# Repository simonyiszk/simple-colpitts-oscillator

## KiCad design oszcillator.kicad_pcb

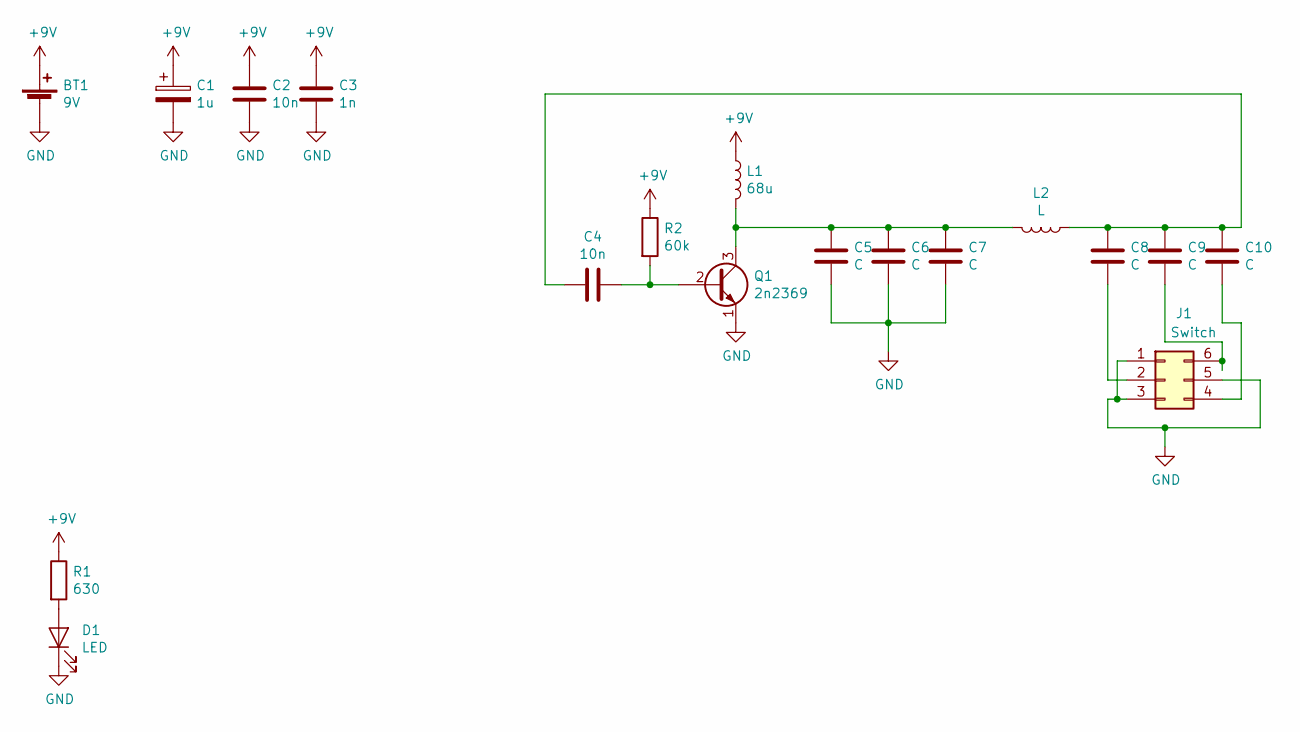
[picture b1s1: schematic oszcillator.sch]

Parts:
BT1: 9V; PinHeader_1x02_P2.54mm_Vertical
C1: 1u; CP_Radial_D6.3mm_P2.50mm
C2, C4: 10n; C_Disc_D3.4mm_W2.1mm_P2.50mm
C3: 1n; C_Disc_D3.4mm_W2.1mm_P2.50mm
C5, C6, C7, C8, C9, C10: C; C_Disc_D3.4mm_W2.1mm_P2.50mm
D1: LED; LED_D3.0mm
J1: Switch; PinSocket_2x03_P2.54mm_Vertical
L1: 68u; L_Axial_L5.3mm_D2.2mm_P10.16mm_Horizontal_Vishay_IM-1
L2: L; PinHeader_1x02_P2.54mm_Vertical
Q1: 2n2369; TO-18-3
R1: 630; R_Axial_DIN0204_L3.6mm_D1.6mm_P2.54mm_Vertical
R2: 60k; R_Box_L8.4mm_W2.5mm_P5.08mm

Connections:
+9V: BT1.1 (+), C1.1, C2.1, C3.1, L1.1, R1.1, R2.1
GND: BT1.2 (-), C1.2, C2.2, C3.2, C5.2, C6.2, C7.2, D1.1 (K), J1.1, J1.3, J1.5, Q1.1 (E)
unnamed: C4.1, Q1.2 (B), R2.2
unnamed: C5.1, C6.1, C7.1, L1.2, L2.2, Q1.3 (C)
unnamed: C8.2, J1.2
unnamed: C9.2, J1.6
unnamed: C4.2, C8.1, C9.1, C10.1, L2.1
unnamed: C10.2, J1.4
unnamed: D1.2 (A), R1.2

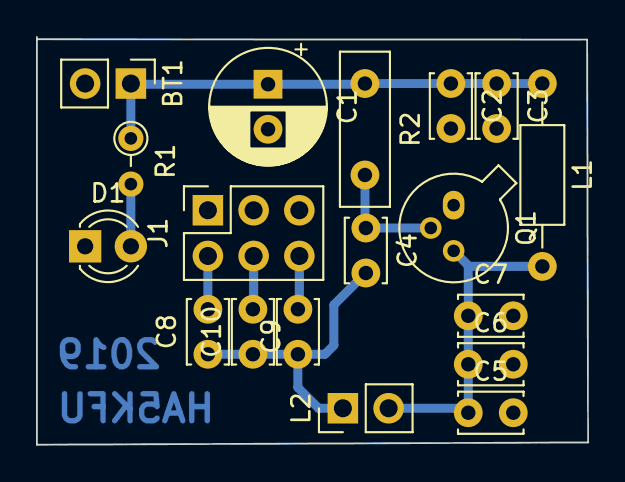
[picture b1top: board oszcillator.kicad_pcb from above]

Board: 2 copper layers, 30.6 x 22.7 mm, 18 parts (0 on the bottom side), 9 nets.
